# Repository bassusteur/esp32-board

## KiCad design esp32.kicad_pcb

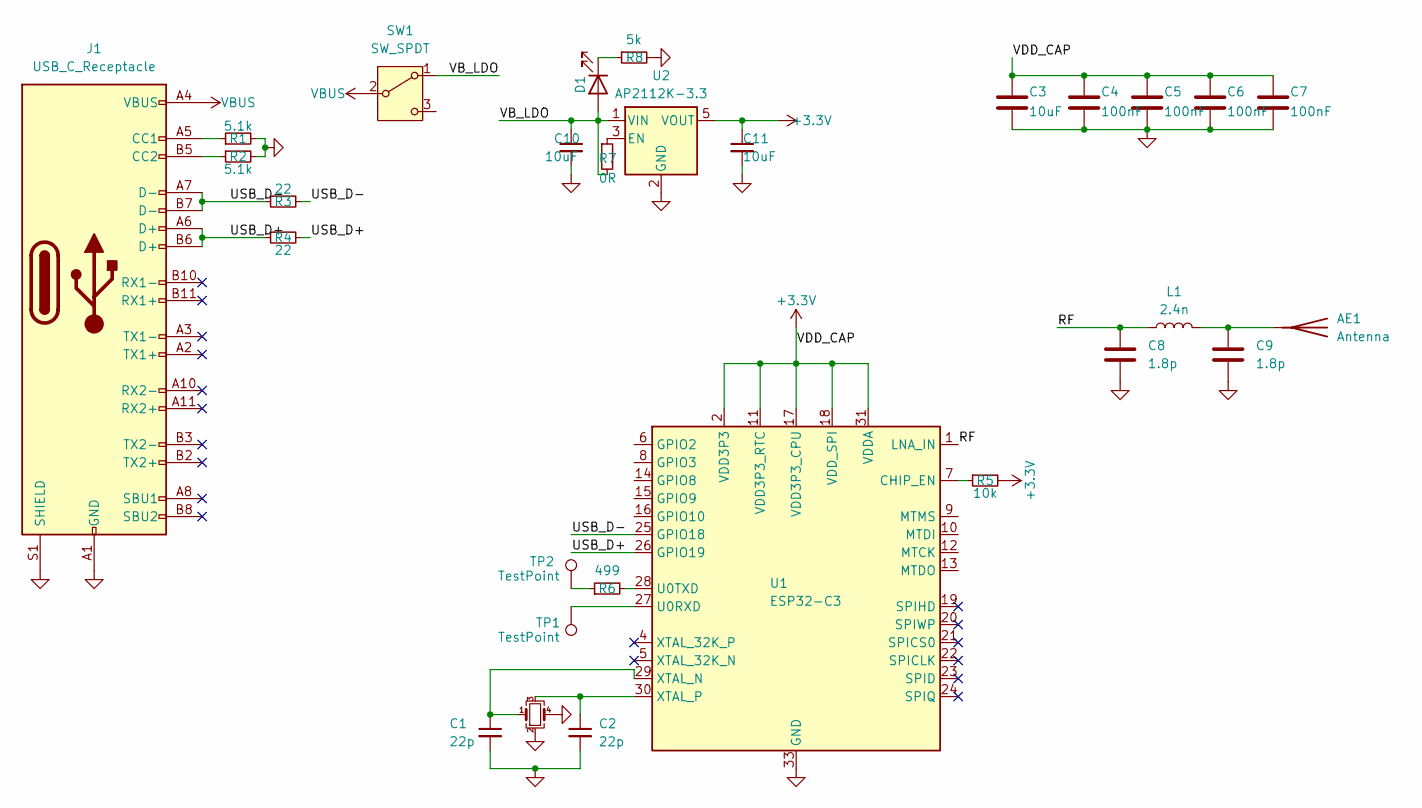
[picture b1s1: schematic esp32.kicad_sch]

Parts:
AE1: Antenna; Texas_SWRA117D_2.4GHz_Left
C1, C2: 22p; C_0201_0603Metric
C3, C10, C11: 10uF; C_0402_1005Metric
C4, C5, C6, C7: 100nF; C_0402_1005Metric
C8, C9: 1.8p; C_0201_0603Metric
D1: LED; LED_0603_1608Metric
J1: USB_C_Receptacle; USB-TYPE-C-TH_TYPEC-300D-BCP16H100
L1: 2.4n; L_0201_0603Metric
R1, R2: 5.1k; R_0402_1005Metric
R3, R4: 22; R_0402_1005Metric
R5: 10k; R_0402_1005Metric
R6: 499; R_0201_0603Metric
R7: 0R; R_0402_1005Metric_Pad0.72x0.64mm_HandSolder
R8: 5k; R_0402_1005Metric
SW1: SW_SPDT; SW_SPDT_CK_JS102011SAQN
TP1, TP2: TestPoint; TestPoint_Pad_D1.5mm
U1: ESP32-C3; QFN-32-1EP_5x5mm_P0.5mm_EP3.7x3.7mm
U2: AP2112K-3.3; SOT-23-5
Y1: Crystal_GND23_Small; Crystal_SMD_2520-4Pin_2.5x2.0mm

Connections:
+3.3V: C3.1, C4.1, C5.1, C6.1, C7.1, C11.1, R5.2, U1.2 (VDD3P3), U1.3 (VDD3P3), U1.11 (VDD3P3_RTC), U1.17 (VDD3P3_CPU), U1.18 (VDD_SPI), U1.31 (VDDA), U1.32 (VDDA), U2.5 (VOUT)
/RF: C8.1, L1.1, U1.1 (LNA_IN)
/USB_D+: J1.A6 (D+), J1.B6 (D+), R4.1, R4.2, U1.26 (GPIO19)
/USB_D-: J1.A7 (D-), J1.B7 (D-), R3.1, R3.2, U1.25 (GPIO18)
/VB_LDO: C10.1, D1.2 (A), R7.2, SW1.1 (A), U2.1 (VIN)
GND: C1.2, C2.2, C3.2, C4.2, C5.2, C6.2, C7.2, C8.2, C9.2, C10.2, C11.2, J1.A1 (GND), J1.A12 (GND), J1.B1 (GND), J1.B12 (GND), J1.S1 (SHIELD), R1.2, R2.2, R8.2, U1.33 (GND), U2.2 (GND), Y1.2, Y1.4
unnamed: AE1.1 (A), C9.1, L1.2
unnamed: D1.1 (K), R8.1
unnamed: J1.A5 (CC1), R1.1
unnamed: J1.B5 (CC2), R2.1
unnamed: R6.1, TP2.1
unnamed: R5.1, U1.7 (CHIP_EN)
unnamed: TP1.1, U1.27 (U0RXD)
unnamed: R6.2, U1.28 (U0TXD)
unnamed: C1.1, U1.29 (XTAL_N), Y1.1
unnamed: C2.1, U1.30 (XTAL_P), Y1.3
unnamed: R7.1, U2.3 (EN)
VBUS: J1.A4 (VBUS), J1.A9 (VBUS), J1.B4 (VBUS), J1.B9 (VBUS), SW1.2 (B)

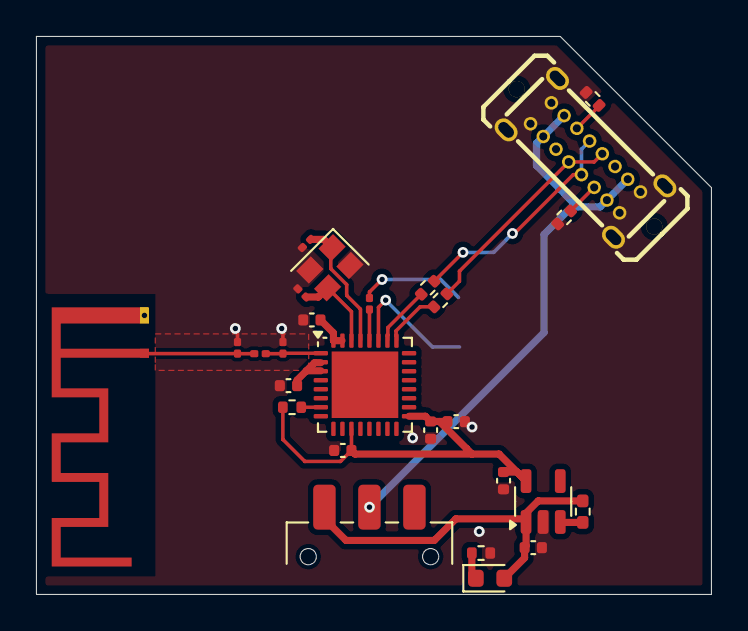
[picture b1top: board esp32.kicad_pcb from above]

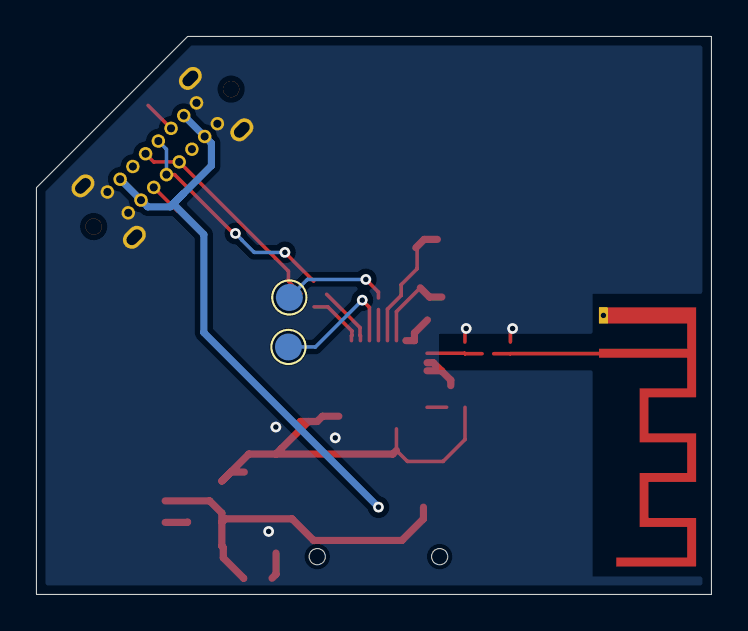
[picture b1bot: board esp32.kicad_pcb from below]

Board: 2 copper layers, 37.5 x 31.0 mm, 29 parts (2 on the bottom side), 18 nets.
